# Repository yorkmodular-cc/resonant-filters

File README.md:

[![CC BY-SA 4.0][cc-by-sa-shield]][cc-by-sa]

This work is licensed under a
[Creative Commons Attribution-ShareAlike 4.0 International License][cc-by-sa].

[![CC BY-SA 4.0][cc-by-sa-image]][cc-by-sa]

[cc-by-sa]: http://creativecommons.org/licenses/by-sa/4.0/
[cc-by-sa-image]: https://licensebuttons.net/l/by-sa/4.0/88x31.png
[cc-by-sa-shield]: https://img.shields.io/badge/License-CC%20BY--SA%204.0-lightgrey.svg

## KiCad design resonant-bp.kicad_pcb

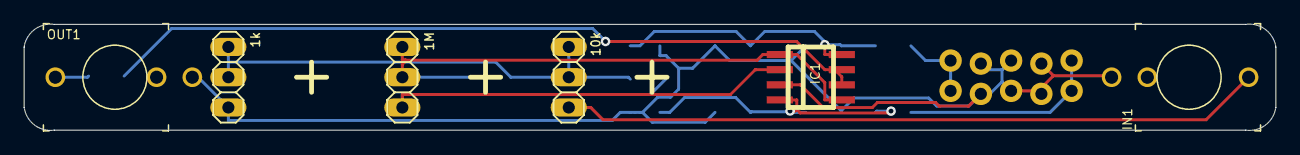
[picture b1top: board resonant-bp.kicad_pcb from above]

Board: 2 copper layers, 105.1 x 8.9 mm, 18 parts (0 on the bottom side), 11 nets.

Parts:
1M, 1k, 10k: PINHD-1X3; 1X03
C1, C2, C5, C6: 0.1u; C_1206_3216Metric_Pad1.42x1.75mm_HandSolder
C3, C4: 10u; C_1206_3216Metric_Pad1.42x1.75mm_HandSolder
D1, D2: 1N4148WS; D_SOD-323_HandSoldering
IC1: TL072D; SO08
IN1: THONKICONNNEW; WQP-PJ301M-12_JACK
OUT1: THONKICONNNEW; WQP-PJ301M-12_JACK
R1: 1k; R_1206_3216Metric_Pad1.42x1.75mm_HandSolder
R2, R3: FERRITE; R_1206_3216Metric_Pad1.42x1.75mm_HandSolder
U$1: EURO_POWER_LOCK; EURO_PWR_HEADER_LOCK

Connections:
+12V: C3.2, C5.2, D1.1, IC1.8, R2.2
-12V: C4.1, C6.1, D2.2, IC1.4, R3.1
/SIG_IN: 10k.3, IN1.P$1_TIP
/SIG_OUT: OUT1.P$1_TIP, R1.2
GND: 1k.3, C3.1, C4.2, C5.1, C6.2, D1.2, D2.1, IC1.3, IN1.P$3_SLEEVE, OUT1.P$3_SLEEVE, U$1.GND1, U$1.GND2, U$1.GND3, U$1.GND4, U$1.GND5, U$1.GND6
unnamed: 1M.1, 1M.2, C1.2, IC1.1, IC1.5
unnamed: 1M.3, C2.1, IC1.2
unnamed: 1k.1, 1k.2, 10k.1, 10k.2, C1.1, C2.2
unnamed: IC1.6, IC1.7, R1.1
unnamed: R2.1, U$1.POS1, U$1.POS2
unnamed: R3.2, U$1.NEG1, U$1.NEG2

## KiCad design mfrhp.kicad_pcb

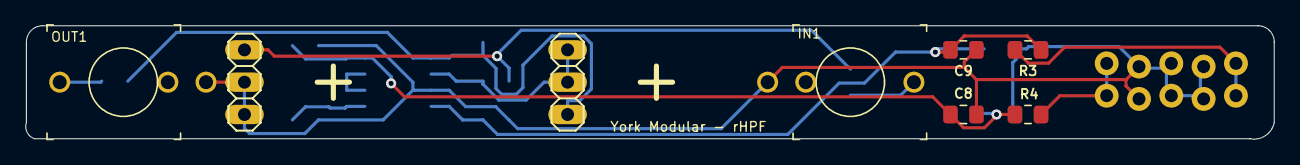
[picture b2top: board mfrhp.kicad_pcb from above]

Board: 2 copper layers, 98.1 x 8.9 mm, 19 parts (0 on the bottom side), 12 nets.

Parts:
C1, C2, C3, C4, C5: 0.1u; C_0805_2012Metric_Pad1.15x1.40mm_HandSolder
C8, C9: 10u; C_0805_2012Metric_Pad1.15x1.40mm_HandSolder
D1, D2: 1N4148WS; D_SOD-323_HandSoldering
IC1: TL072D; SO08
IN1: THONKICONNNEW; WQP-PJ301M-12_JACK
JP1, JP2: PINHD-1X3; 1X03
OUT1: THONKICONNNEW; WQP-PJ301M-12_JACK
R1: 1k; R_0805_2012Metric_Pad1.15x1.40mm_HandSolder
R2: 100k; R_0805_2012Metric_Pad1.15x1.40mm_HandSolder
R3, R4: FERRITE; R_0805_2012Metric_Pad1.15x1.40mm_HandSolder
U$1: EURO_POWER_LOCK; EURO_PWR_HEADER_LOCK

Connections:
+12V: C4.1, C8.1, D1.1, IC1.8, R4.2
-12V: C5.1, C9.2, D2.2, IC1.4, R3.1
GND: C4.2, C5.2, C8.2, C9.1, D1.2, D2.1, IC1.3, IN1.P$3_SLEEVE, JP2.2, JP2.3, OUT1.P$3_SLEEVE, R2.1, U$1.GND1, U$1.GND2, U$1.GND3, U$1.GND4, U$1.GND5, U$1.GND6
unnamed: C1.1, IN1.P$1_TIP
unnamed: C1.2, C2.2, C3.1, JP2.1
unnamed: C2.1, IC1.1, JP1.3, R1.1
unnamed: C3.2, IC1.2, JP1.1, JP1.2
unnamed: IC1.5, R2.2
unnamed: IC1.6, IC1.7
unnamed: OUT1.P$1_TIP, R1.2
unnamed: R3.2, U$1.NEG1, U$1.NEG2
unnamed: R4.1, U$1.POS1, U$1.POS2

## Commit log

2022-05-13 Create LICENSE
